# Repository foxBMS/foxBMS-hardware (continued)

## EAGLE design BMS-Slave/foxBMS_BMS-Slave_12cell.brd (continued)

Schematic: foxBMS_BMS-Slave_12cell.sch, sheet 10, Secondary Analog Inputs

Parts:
C1001: 100nF, 20%, 16V; C_SMD_0603_(1608)_R_KEMET_REV01
C1002, C1003, C1006, C1007, C1008: 1uF, 20%, 16V; C_SMD_0603_(1608)_R_KEMET_REV01
C1004, C1005: 10nF, 100V, 10%; C_SMD_0603_(1608)_R_KEMET_REV01
IC1001, IC1002, IC1005: ADG728BRUZ; SOP65P638X110-16N
IC1003, IC1004: LTC6255CS6; IC_SMD_TSOT-23-6_(S6)_R_LINEAR_REV01
R1001, R1002, R1003, R1004, R1005, R1006, R1007, R1008: 10,0K_0603_R_VISHAY_1%_TK100_REV_01; R_SMD_0603_R_VISHAY_REV01
R1009, R1010: 100R_0603_R_VISHAY_1%_TK100_REV_01; R_SMD_0603_R_VISHAY_REV01
SJ1001, SJ1002: OPT; CUSTOM_JUMPER_SJ

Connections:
+3.0V_VREF2_1: C1001.2, R1001.2, R1002.2, R1003.2, R1004.2, R1005.2, R1006.2, R1007.2, R1008.2; also elsewhere on the board
+5.0V_VREG_1: C1002.2, C1003.2, C1006.2, C1007.2, C1008.2, IC1001.2 (!RESET), IC1001.13 (VCC), IC1002.2 (!RESET), IC1002.13 (VCC), IC1002.15 (A1), IC1003.6 (V+), IC1004.6 (V+), IC1005.2 (!RESET), IC1005.13 (VCC), IC1005.16 (A0); also elsewhere on the board
FUSED_VBAT-: C1001.1, C1002.1, C1003.1, C1004.1, C1005.1, C1006.1, C1007.1, C1008.1, IC1001.14 (GND), IC1001.15 (A1), IC1001.16 (A0), IC1002.14 (GND), IC1002.16 (A0), IC1003.2 (V-), IC1004.2 (V-), IC1005.14 (GND), IC1005.15 (A1), SJ1001.2, SJ1002.2; also elsewhere on the board
unnamed: IC1003.1 (VOUT), IC1003.4 (-), R1009.1
unnamed: IC1003.5 (!SHDN), SJ1001.1
unnamed: IC1004.1 (VOUT), IC1004.4 (-), R1010.1
unnamed: IC1004.5 (!SHDN), SJ1002.1
SECONDARY-ANALOG-IN_0: IC1005.4 (S1); also elsewhere on the board
SECONDARY-ANALOG-IN_1: IC1005.5 (S2); also elsewhere on the board
SECONDARY-ANALOG-IN_2: IC1005.6 (S3); also elsewhere on the board
SECONDARY-ANALOG-IN_3: IC1005.7 (S4); also elsewhere on the board
SECONDARY-ANALOG-IN_4: IC1005.12 (S5); also elsewhere on the board
SECONDARY-ANALOG-IN_5: IC1005.11 (S6); also elsewhere on the board
SECONDARY-ANALOG-IN_6: IC1005.10 (S7); also elsewhere on the board
SECONDARY-ANALOG-IN_7: IC1005.9 (S8); also elsewhere on the board
SECONDARY-ANALOG-IN_8: IC1002.4 (S1); also elsewhere on the board
SECONDARY-ANALOG-IN_9: IC1002.5 (S2); also elsewhere on the board
SECONDARY-ANALOG-IN_10: IC1002.6 (S3); also elsewhere on the board
SECONDARY-ANALOG-IN_11: IC1002.7 (S4); also elsewhere on the board
SECONDARY-ANALOG-IN_12: IC1002.12 (S5); also elsewhere on the board
SECONDARY-ANALOG-IN_13: IC1002.11 (S6); also elsewhere on the board
SECONDARY-ANALOG-IN_14: IC1002.10 (S7); also elsewhere on the board
SECONDARY-ANALOG-IN_15: IC1002.9 (S8); also elsewhere on the board
SECONDARY-MUX-DATA_TEMP: C1004.2, R1009.2; also elsewhere on the board
SECONDARY-MUX-DATA_USER: C1005.2, R1010.2; also elsewhere on the board
SECONDARY-OPA_TEMP: IC1001.8 (D), IC1003.3 (+)
SECONDARY-OPA_USER: IC1002.8 (D), IC1004.3 (+), IC1005.8 (D)
SECONDARY-SCL_1: IC1001.1 (SCL), IC1002.1 (SCL), IC1005.1 (SCL); also elsewhere on the board
SECONDARY-SDA_1: IC1001.3 (SDA), IC1002.3 (SDA), IC1005.3 (SDA); also elsewhere on the board
SECONDARY-T-SENSOR_0: IC1001.4 (S1), R1008.1; also elsewhere on the board
SECONDARY-T-SENSOR_1: IC1001.5 (S2), R1007.1; also elsewhere on the board
SECONDARY-T-SENSOR_2: IC1001.6 (S3), R1006.1; also elsewhere on the board
SECONDARY-T-SENSOR_3: IC1001.7 (S4), R1005.1; also elsewhere on the board
SECONDARY-T-SENSOR_4: IC1001.12 (S5), R1004.1; also elsewhere on the board
SECONDARY-T-SENSOR_5: IC1001.11 (S6), R1003.1; also elsewhere on the board
SECONDARY-T-SENSOR_6: IC1001.10 (S7), R1002.1; also elsewhere on the board
SECONDARY-T-SENSOR_7: IC1001.9 (S8), R1001.1; also elsewhere on the board

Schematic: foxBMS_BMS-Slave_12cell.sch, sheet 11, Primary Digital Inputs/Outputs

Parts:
C1101: 100nF, 20%, 16V; C_SMD_0603_(1608)_R_KEMET_REV01
IC1101: PCA8574TS; SOP65P640X150-20N
R1101, R1102, R1103, R1104, R1105, R1106, R1107, R1108: 10,0K_0603_R_VISHAY_1%_TK100_REV_01; R_SMD_0603_R_VISHAY_REV01

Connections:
+5.0V_VREG_0: C1101.2, IC1101.5 (VDD), R1101.2, R1102.2, R1103.2, R1104.2, R1105.2, R1106.2, R1107.2, R1108.2; also elsewhere on the board
FUSED_VBAT-: C1101.1, IC1101.6 (A0), IC1101.7 (A1), IC1101.9 (A2), IC1101.15 (VSS); also elsewhere on the board
PRIMARY-DIGITAL-IO_0: IC1101.10 (P0), R1101.1; also elsewhere on the board
PRIMARY-DIGITAL-IO_1: IC1101.11 (P1), R1102.1; also elsewhere on the board
PRIMARY-DIGITAL-IO_2: IC1101.12 (P2), R1103.1; also elsewhere on the board
PRIMARY-DIGITAL-IO_3: IC1101.14 (P3), R1104.1; also elsewhere on the board
PRIMARY-DIGITAL-IO_4: IC1101.16 (P4), R1105.1; also elsewhere on the board
PRIMARY-DIGITAL-IO_5: IC1101.17 (P5), R1106.1; also elsewhere on the board
PRIMARY-DIGITAL-IO_6: IC1101.19 (P6), R1107.1; also elsewhere on the board
PRIMARY-DIGITAL-IO_7: IC1101.20 (P7), R1108.1; also elsewhere on the board
PRIMARY-SCL_0: IC1101.2 (SCL); also elsewhere on the board
PRIMARY-SDA_0: IC1101.4 (SDA); also elsewhere on the board

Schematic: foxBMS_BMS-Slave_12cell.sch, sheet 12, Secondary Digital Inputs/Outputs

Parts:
C1201: 100nF, 20%, 16V; C_SMD_0603_(1608)_R_KEMET_REV01
IC1201: PCA8574TS; SOP65P640X150-20N
R1201, R1202, R1203, R1204, R1205, R1206, R1207, R1208: 10,0K_0603_R_VISHAY_1%_TK100_REV_01; R_SMD_0603_R_VISHAY_REV01

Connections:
+5.0V_VREG_1: C1201.2, IC1201.5 (VDD), R1201.2, R1202.2, R1203.2, R1204.2, R1205.2, R1206.2, R1207.2, R1208.2; also elsewhere on the board
FUSED_VBAT-: C1201.1, IC1201.6 (A0), IC1201.7 (A1), IC1201.9 (A2), IC1201.15 (VSS); also elsewhere on the board
SECONDARY-DIGITAL-IO_0: IC1201.10 (P0), R1201.1; also elsewhere on the board
SECONDARY-DIGITAL-IO_1: IC1201.11 (P1), R1202.1; also elsewhere on the board
SECONDARY-DIGITAL-IO_2: IC1201.12 (P2), R1203.1; also elsewhere on the board
SECONDARY-DIGITAL-IO_3: IC1201.14 (P3), R1204.1; also elsewhere on the board
SECONDARY-DIGITAL-IO_4: IC1201.16 (P4), R1205.1; also elsewhere on the board
SECONDARY-DIGITAL-IO_5: IC1201.17 (P5), R1206.1; also elsewhere on the board
SECONDARY-DIGITAL-IO_6: IC1201.19 (P6), R1207.1; also elsewhere on the board
SECONDARY-DIGITAL-IO_7: IC1201.20 (P7), R1208.1; also elsewhere on the board
SECONDARY-SCL_1: IC1201.2 (SCL); also elsewhere on the board
SECONDARY-SDA_1: IC1201.4 (SDA); also elsewhere on the board

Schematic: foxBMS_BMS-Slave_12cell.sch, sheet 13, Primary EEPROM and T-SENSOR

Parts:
C1301, C1302: 100nF, 20%, 16V; C_SMD_0603_(1608)_R_KEMET_REV01
IC1301: M24M02-DR; SOIC127P600X175-8N
IC1302: MCP9800A0T-M/OT; SOT95P280X145-5N
R1301, R1302: 10,0K_0603_R_VISHAY_1%_TK100_REV_01; R_SMD_0603_R_VISHAY_REV01

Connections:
+5.0V_VREG_0: C1301.2, C1302.2, IC1301.8 (VCC), IC1302.1 (VDD), R1301.2, R1302.2; also elsewhere on the board
FUSED_VBAT-: C1301.1, C1302.1, IC1301.3 (E2), IC1301.4 (VSS), IC1302.2 (GND); also elsewhere on the board
unnamed: IC1301.7 (!WC), R1302.1
PRIMARY-SCL_0: IC1301.6 (SCL), IC1302.4 (SCLK); also elsewhere on the board
PRIMARY-SDA_0: IC1301.5 (SDA), IC1302.5 (SDA); also elsewhere on the board
PRIMARY-TEMP-ALERT: IC1302.3 (ALERT), R1301.1; also elsewhere on the board

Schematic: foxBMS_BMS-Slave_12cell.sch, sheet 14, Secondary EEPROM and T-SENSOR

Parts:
C1401, C1402: 100nF, 20%, 16V; C_SMD_0603_(1608)_R_KEMET_REV01
IC1401: M24M02-DR; SOIC127P600X175-8N
IC1402: MCP9800A0T-M/OT; SOT95P280X145-5N
R1401, R1402: 10,0K_0603_R_VISHAY_1%_TK100_REV_01; R_SMD_0603_R_VISHAY_REV01

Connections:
+5.0V_VREG_1: C1401.2, C1402.2, IC1401.8 (VCC), IC1402.1 (VDD), R1401.2, R1402.2; also elsewhere on the board
FUSED_VBAT-: C1401.1, C1402.1, IC1401.3 (E2), IC1401.4 (VSS), IC1402.2 (GND); also elsewhere on the board
unnamed: IC1401.7 (!WC), R1402.1
SECONDARY-SCL_1: IC1401.6 (SCL), IC1402.4 (SCLK); also elsewhere on the board
SECONDARY-SDA_1: IC1401.5 (SDA), IC1402.5 (SDA); also elsewhere on the board
SECONDARY-TEMP-ALERT: IC1402.3 (ALERT), R1401.1; also elsewhere on the board

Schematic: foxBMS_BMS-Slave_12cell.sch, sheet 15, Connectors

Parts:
C1501, C1502, C1503, C1504, C1505, C1506, C1507, C1508: 100nF, 20%, 16V; C_SMD_0603_(1608)_R_KEMET_REV01
X1501, X1502: MA09-2
X1503: 43045-2400_MOLEX_24PIN; X_TH_MOLEX_43045-2400_R_REV01
X1504, X1505: MA05-2
X1506, X1507: 43045-1600_MOLEX_16PIN; X_TH_MOLEX_43045-1600_R_REV01
X1508: MA10-2
X1509, X1510, X1511, X1512, X1513, X1514: 43045-0200_MOLEX_2PIN; X_TH_MOLEX_43045-0200_R_REV01
X1515: MA02-2_TH; MA02-2

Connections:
+3.0V_VREF2_0: C1501.2, C1506.2, X1501.17, X1508.1; also elsewhere on the board
+3.0V_VREF2_1: C1502.2, C1507.2, X1502.17, X1508.2; also elsewhere on the board
+5.0V_VREG_0: C1503.2, C1505.2, X1504.9, X1508.3; also elsewhere on the board
+5.0V_VREG_1: C1504.2, C1508.2, X1505.9, X1508.4; also elsewhere on the board
CELL_0+: X1503.2; also elsewhere on the board
CELL_0-: X1503.13; also elsewhere on the board
CELL_1+: X1503.14; also elsewhere on the board
CELL_2+: X1503.3; also elsewhere on the board
CELL_3+: X1503.15; also elsewhere on the board
CELL_4+: X1503.4; also elsewhere on the board
CELL_5+: X1503.16; also elsewhere on the board
CELL_6+: X1503.5; also elsewhere on the board
CELL_7+: X1503.17; also elsewhere on the board
CELL_8+: X1503.6; also elsewhere on the board
CELL_9+: X1503.18; also elsewhere on the board
CELL_10+: X1503.7; also elsewhere on the board
CELL_11+: X1503.19; also elsewhere on the board
EXT_DC_IN+: X1513.1, X1514.1, X1515.1, X1515.3; also elsewhere on the board
EXT_DC_IN-: X1513.2, X1514.2, X1515.2, X1515.4; also elsewhere on the board
FUSED_VBAT-: C1501.1, C1502.1, C1503.1, C1504.1, C1505.1, C1506.1, C1507.1, C1508.1, X1501.18, X1502.18, X1504.10, X1505.10, X1506.9, X1506.10, X1506.11, X1506.12, X1506.13, X1506.14, X1506.15, X1506.16, X1507.9, X1507.10, X1507.11, X1507.12, X1507.13, X1507.14, X1507.15, X1507.16, X1508.19, X1508.20; also elsewhere on the board
PRIMARY-ANALOG-IN_0: X1501.1; also elsewhere on the board
PRIMARY-ANALOG-IN_1: X1501.2; also elsewhere on the board
PRIMARY-ANALOG-IN_2: X1501.3; also elsewhere on the board
PRIMARY-ANALOG-IN_3: X1501.4; also elsewhere on the board
PRIMARY-ANALOG-IN_4: X1501.5; also elsewhere on the board
PRIMARY-ANALOG-IN_5: X1501.6; also elsewhere on the board
PRIMARY-ANALOG-IN_6: X1501.7; also elsewhere on the board
PRIMARY-ANALOG-IN_7: X1501.8; also elsewhere on the board
PRIMARY-ANALOG-IN_8: X1501.9; also elsewhere on the board
PRIMARY-ANALOG-IN_9: X1501.10; also elsewhere on the board
PRIMARY-ANALOG-IN_10: X1501.11; also elsewhere on the board
PRIMARY-ANALOG-IN_11: X1501.12; also elsewhere on the board
PRIMARY-ANALOG-IN_12: X1501.13; also elsewhere on the board
PRIMARY-ANALOG-IN_13: X1501.14; also elsewhere on the board
PRIMARY-ANALOG-IN_14: X1501.15; also elsewhere on the board
PRIMARY-ANALOG-IN_15: X1501.16; also elsewhere on the board
PRIMARY-DIGITAL-IO_0: X1504.1; also elsewhere on the board
PRIMARY-DIGITAL-IO_1: X1504.2; also elsewhere on the board
PRIMARY-DIGITAL-IO_2: X1504.3; also elsewhere on the board
PRIMARY-DIGITAL-IO_3: X1504.4; also elsewhere on the board
PRIMARY-DIGITAL-IO_4: X1504.5; also elsewhere on the board
PRIMARY-DIGITAL-IO_5: X1504.6; also elsewhere on the board
PRIMARY-DIGITAL-IO_6: X1504.7; also elsewhere on the board
PRIMARY-DIGITAL-IO_7: X1504.8; also elsewhere on the board
PRIMARY-GPIO1-OPT: X1508.5; also elsewhere on the board
PRIMARY-GPIO2-OPT: X1508.7; also elsewhere on the board
PRIMARY-GPIO3-OPT: X1508.9; also elsewhere on the board
PRIMARY-GPIO4-OPT: X1508.11; also elsewhere on the board
PRIMARY-GPIO5-OPT: X1508.13; also elsewhere on the board
PRIMARY-IN+: X1509.1; also elsewhere on the board
PRIMARY-IN-: X1509.2; also elsewhere on the board
PRIMARY-OUT+: X1510.1; also elsewhere on the board
PRIMARY-OUT-: X1510.2; also elsewhere on the board
PRIMARY-T-SENSOR_0: X1506.1; also elsewhere on the board
PRIMARY-T-SENSOR_1: X1506.2; also elsewhere on the board
PRIMARY-T-SENSOR_2: X1506.3; also elsewhere on the board
PRIMARY-T-SENSOR_3: X1506.4; also elsewhere on the board
PRIMARY-T-SENSOR_4: X1506.5; also elsewhere on the board
PRIMARY-T-SENSOR_5: X1506.6; also elsewhere on the board
PRIMARY-T-SENSOR_6: X1506.7; also elsewhere on the board
PRIMARY-T-SENSOR_7: X1506.8; also elsewhere on the board
PRIMARY-TEMP-ALERT: X1508.17; also elsewhere on the board
PRIMARY-WDT: X1508.15; also elsewhere on the board
SECONDARY-ANALOG-IN_0: X1502.1; also elsewhere on the board
SECONDARY-ANALOG-IN_1: X1502.2; also elsewhere on the board
SECONDARY-ANALOG-IN_2: X1502.3; also elsewhere on the board
SECONDARY-ANALOG-IN_3: X1502.4; also elsewhere on the board
SECONDARY-ANALOG-IN_4: X1502.5; also elsewhere on the board
SECONDARY-ANALOG-IN_5: X1502.6; also elsewhere on the board
SECONDARY-ANALOG-IN_6: X1502.7; also elsewhere on the board
SECONDARY-ANALOG-IN_7: X1502.8; also elsewhere on the board
SECONDARY-ANALOG-IN_8: X1502.9; also elsewhere on the board
SECONDARY-ANALOG-IN_9: X1502.10; also elsewhere on the board
SECONDARY-ANALOG-IN_10: X1502.11; also elsewhere on the board
SECONDARY-ANALOG-IN_11: X1502.12; also elsewhere on the board
SECONDARY-ANALOG-IN_12: X1502.13; also elsewhere on the board
SECONDARY-ANALOG-IN_13: X1502.14; also elsewhere on the board
SECONDARY-ANALOG-IN_14: X1502.15; also elsewhere on the board
SECONDARY-ANALOG-IN_15: X1502.16; also elsewhere on the board
SECONDARY-DIGITAL-IO_0: X1505.1; also elsewhere on the board
SECONDARY-DIGITAL-IO_1: X1505.2; also elsewhere on the board
SECONDARY-DIGITAL-IO_2: X1505.3; also elsewhere on the board
SECONDARY-DIGITAL-IO_3: X1505.4; also elsewhere on the board
SECONDARY-DIGITAL-IO_4: X1505.5; also elsewhere on the board
SECONDARY-DIGITAL-IO_5: X1505.6; also elsewhere on the board
SECONDARY-DIGITAL-IO_6: X1505.7; also elsewhere on the board
SECONDARY-DIGITAL-IO_7: X1505.8; also elsewhere on the board
SECONDARY-GPIO1-OPT: X1508.6; also elsewhere on the board
SECONDARY-GPIO2-OPT: X1508.8; also elsewhere on the board
SECONDARY-GPIO3-OPT: X1508.10; also elsewhere on the board
SECONDARY-GPIO4-OPT: X1508.12; also elsewhere on the board
SECONDARY-GPIO5-OPT: X1508.14; also elsewhere on the board
SECONDARY-IN+: X1511.1; also elsewhere on the board
SECONDARY-IN-: X1511.2; also elsewhere on the board
SECONDARY-OUT+: X1512.1; also elsewhere on the board
SECONDARY-OUT-: X1512.2; also elsewhere on the board
SECONDARY-T-SENSOR_0: X1507.1; also elsewhere on the board
SECONDARY-T-SENSOR_1: X1507.2; also elsewhere on the board
SECONDARY-T-SENSOR_2: X1507.3; also elsewhere on the board
SECONDARY-T-SENSOR_3: X1507.4; also elsewhere on the board
SECONDARY-T-SENSOR_4: X1507.5; also elsewhere on the board
SECONDARY-T-SENSOR_5: X1507.6; also elsewhere on the board
SECONDARY-T-SENSOR_6: X1507.7; also elsewhere on the board
SECONDARY-T-SENSOR_7: X1507.8; also elsewhere on the board
SECONDARY-TEMP-ALERT: X1508.18; also elsewhere on the board
SECONDARY-WDT: X1508.16; also elsewhere on the board
VBAT+: X1503.8; also elsewhere on the board
VBAT-: X1503.1; also elsewhere on the board

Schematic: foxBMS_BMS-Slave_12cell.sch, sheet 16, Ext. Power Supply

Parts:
C1601: 1,00µF_0805_25V_X7R_KEMET; C_SMD_0805_(2012)_R_KEMET_REV01
C1602, C1603: 10µF_1210_25V_X7R; 1210
C1604: 100nF, 20%, 16V; C_SMD_0603_(1608)_R_KEMET_REV01
C1605: 1uF, 20%, 16V; C_SMD_0603_(1608)_R_KEMET_REV01
C1606: 470PF_0805_50V_X7R_KEMET; C_SMD_0805_(2012)_R_KEMET_REV01
C1607: 4,7NF_1812; 1812
C1608, C1609, C1610: 4,70µF_1206_25V_X7R_KEMET; C_SMD_1206_(3216)_R_KEMET_REV01
D1601, D1603: DI_DFLS1100; POWER_DI_123
D1602: DI_DFLZ36; POWER_DI_123
D1604: DI_PDS3200; POWER_DI_5
D1605: MMSZ5263B; SOD123
F1601: 1,250A_LITTELFUSE_466_1206; R_SMD_CHIP_1206_R_LITTLEFUSE_REV_01
IC1601: LT8302; S8E
L1601: WE-74404042100; WE-LQS
R1601: 390K_0603_R_VISHAY_1%_TK100_REV_01; R_SMD_0603_R_VISHAY_REV01
R1602: 86,6K_0603_R_VISHAY_1%_TK100_REV_01; R_SMD_0603_R_VISHAY_REV01
R1603: 39,0R_0805_R_VISHAY_1%_TK100_REV_01; R_SMD_0805_R_VISHAY_REV01
R1604: DUMMY_R_CHIP_0603_R_VISHAY; R_SMD_0603_R_VISHAY_REV01
R1605: 127K_0603_R_VISHAY_1%_TK100_REV_01; R_SMD_0603_R_VISHAY_REV01
R1606: 10,0K_0603_R_VISHAY_1%_TK100_REV_01; R_SMD_0603_R_VISHAY_REV01
TP1601, TP1602, TP1603: CUSTOM_PAD_PAD_2.0X1.5MM; CUSTOM_PAD_PAD2.0X1.5MM
TR1601: WE_750313457; WUERTH_CUSTOM
X1601: MA02-1_TH; MA02-1A

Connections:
EXT_DC_IN+: F1601.P$1; also elsewhere on the board
EXT_DC_IN-: C1601.P$1, C1602.P$1, C1603.P$1, C1604.1, C1605.1, C1607.P$1, IC1601.4 (GND), IC1601.P$1 (GND), R1602.1, R1606.1, TP1601.P$1; also elsewhere on the board
EXT_DC_ISO+: C1608.P$2, C1609.P$2, C1610.P$2, D1604.K (C), D1605.C (K), X1601.1; also elsewhere on the board
FUSED_VBAT-: C1607.P$2, C1608.P$1, C1609.P$1, C1610.P$1, D1605.A, TP1603.P$1, TR1601.8 (PIN8), X1601.2; also elsewhere on the board
unnamed: C1604.2, IC1601.1 (EN/UVLO), R1601.1, R1602.2
unnamed: C1605.2, IC1601.2 (INTVCC)
unnamed: TR1601.6 (PIN6), TR1601.7 (PIN7)
unnamed: IC1601.7 (R_REF), R1604.2, R1606.2
unnamed: IC1601.6 (R_FB), R1605.1
unnamed: D1603.A, IC1601.5 (SW), R1603.1, R1605.2, TR1601.1 (PIN2), TR1601.2 (PIN2)
unnamed: IC1601.8 (TC), R1604.1
unnamed: D1604.A1 (A), D1604.A2 (A), TR1601.5 (PIN5)
unnamed: C1606.P$1, R1603.2
unnamed: D1601.A, F1601.P$2
unnamed: C1601.P$2, D1601.K (C), L1601.1, TP1602.P$1
unnamed: D1602.K (C), D1603.K (C)
unnamed: C1602.P$2, C1603.P$2, C1606.P$2, D1602.A, IC1601.3 (V_IN), L1601.2, R1601.2, TR1601.3 (PIN4), TR1601.4 (PIN4)

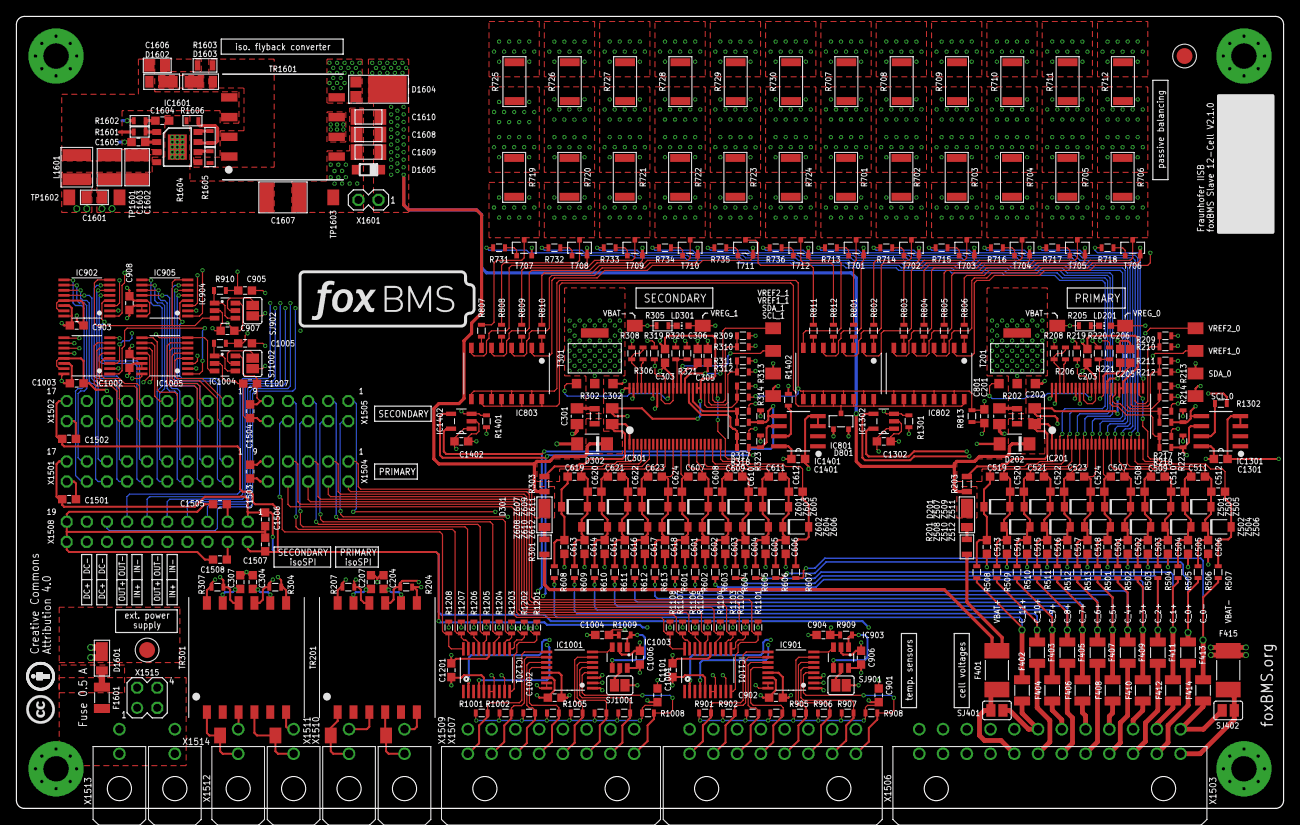
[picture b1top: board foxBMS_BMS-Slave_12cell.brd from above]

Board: 6 copper layers, 160.0 x 100.0 mm, 405 parts (0 on the bottom side), 274 nets.

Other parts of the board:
U$55, U$56: FIDUCIAL_1MM

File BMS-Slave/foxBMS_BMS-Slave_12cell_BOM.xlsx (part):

Pos. | Qty | Value | Device | Package | Parts | Description | Farnell | Digi-Key
 | Resistors
1 | 12 | 0R | 0,00R_0603_R_VISHAY_REV_01 | R_SMD_0603_R_VISHAY_REV01 | R210, R212, R214, R216, R218, R220, R310, R312, R314, R316, R318, R320 | 0,00R SMD - CHIP - Dickschichtwiderstand | 1469739
2 | 2 | 1.21k, 1%, 1/10W | 1,21K_0603_R_VISHAY_1%_TK100_REV_01 | R_SMD_0603_R_VISHAY_REV01 | R208, R308 | 1,21K SMD - CHIP - Dickschichtwiderstand | 1652852
3 | 36 | 10,0K_0603_R_VISHAY_1%_TK100_REV_01 | 10,0K_0603_R_VISHAY_1%_TK100_REV_01 | R_SMD_0603_R_VISHAY_REV01 | R813, R901, R902, R903, R904, R905, R906, R907, R908, R1001, R1002, R1003, R100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 | 10,0K SMD - CHIP - Dickschichtwiderstand | 1469748
4 | 4 | 100R, 1%, 1/10W | 100R_0805_R_VISHAY_1%_TK100_REV_01 | R_SMD_0805_R_VISHAY_REV01 | R202, R203, R302, R303 | 100R SMD - CHIP - Dickschichtwiderstand | 1469862
5 | 30 | 100R_0603_R_VISHAY_1%_TK100_REV_01 | 100R_0603_R_VISHAY_1%_TK100_REV_01 | R_SMD_0603_R_VISHAY_REV01 | R501, R502, R503, R504, R505, R506, R507, R508, R509, R510, R511, R512, R513, R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 | 100R SMD - CHIP - Dickschichtwiderstand | 1469752
6 | 4 | 120R, 1%, 1/10W | 120R_0603_R_VISHAY_1%_TK100_REV_01 | R_SMD_0603_R_VISHAY_REV01 | R204, R207, R304, R307 | 120R SMD - CHIP - Dickschichtwiderstand | 1652832
7 | 12 | 150R_0603_R_VISHAY_1%_TK100_REV_01 | 150R_0603_R_VISHAY_1%_TK100_REV_01 | R_SMD_0603_R_VISHAY_REV01 | R801, R802, R803, R804, R805, R806, R807, R808, R809, R810, R811, R812 | 150R SMD - CHIP - Dickschichtwiderstand | 1469760
8 | 2 | 1M, 10%, 1/10W | 1,00M_0603_R_VISHAY_1%_TK100_REV_01 | R_SMD_0603_R_VISHAY_REV01 | R219, R319 | 1,00M SMD - CHIP - Dickschichtwiderstand | 1469746
9 | 2 | 1M, 10%, 1/10W | 330R_0603_R_VISHAY_1%_TK100_REV_01 | R_SMD_0603_R_VISHAY_REV01 | R205, R305 | 330R SMD - CHIP - Dickschichtwiderstand | 2141320
10 | 12 | 3.3k, 10%, 1/10W | 3,30K_0603_R_VISHAY_1%_TK100_REV_01 | R_SMD_0603_R_VISHAY_REV01 | R713, R714, R715, R716, R717, R718, R731, R732, R733, R734, R735, R736 | 3,30K SMD - CHIP - Dickschichtwiderstand | 1469793
11 | 4 | 4.7k, 10%, 1/10W | 1,20K_0603_R_VISHAY_1%_TK100_REV_01 | R_SMD_0603_R_VISHAY_REV01 | R222, R223, R322, R323 | 1,20K SMD - CHIP - Dickschichtwiderstand | 1469741
12 | 24 | 75R, 10%, 0.4W | 68,0R_2010_R_YAGEO_5%_TK100_REV_01 | R_SMD_2010_R_YAGEO_REV01 | R701, R702, R703, R704, R705, R706, R707, R708, R709, R710, R711, R712, R719, R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 | 68,0R SMD - CHIP - Dickschichtwiderstand | 2323988
13 | 2 | 806, 1%, 1/10W | 820R_0603_R_VISHAY_1%_TK100_REV_01 | R_SMD_0603_R_VISHAY_REV01 | R206, R306 | 820R SMD - CHIP - Dickschichtwiderstand | 1469841
14 | 1 | 402K_0603_R_VISHAY_1%_TK100_REV_01 | 390K_0603_R_VISHAY_1%_TK100_REV_01 | R_SMD_0603_R_VISHAY_REV01 | R1601 | 390K SMD - CHIP - Dickschichtwiderstand | 2303278
15 | 1 | 86,6K_0603_R_VISHAY_1%_TK100_REV_01 | 86,6K_0603_R_VISHAY_1%_TK100_REV_01 | R_SMD_0603_R_VISHAY_REV01 | R1602 | 86,6K SMD - CHIP - Dickschichtwiderstand | 2059490
16 | 1 | 39,0R_0805_R_VISHAY_1%_TK100_REV_01 | 39,0R_0805_R_VISHAY_1%_TK100_REV_01 | R_SMD_0805_R_VISHAY_REV01 | R1603 | 39,0R SMD - CHIP - Dickschichtwiderstand | 1750736
17 | 1 | 127K_0603_R_VISHAY_1%_TK100_REV_01 | 127K_0603_R_VISHAY_1%_TK100_REV_01 | R_SMD_0603_R_VISHAY_REV01 | R1605 | 127K SMD - CHIP - Dickschichtwiderstand | 2059500
18 | 2 | 0,00R_0805_R_VISHAY_REV_01 | 0,00R_0805_R_VISHAY_REV_01 | R_SMD_0805_R_VISHAY_REV01 | R201, R301 | 0,00R SMD - CHIP - Dickschichtwiderstand | 2057661
 | Capacitors
19 | 4 | 100nF, 10%, 100V | 100NF_0805_100V_X7R_MULTICOMP | C_SMD_0805_(2012)_R_MULTICOMP_REV01 | C201 C202 C301 C302 | 100nF Keramik-Kondensator | 2320821
20 | 18 | 100nF, 20%, 16V | 100NF_0603_16V_X7R_KEMET | C_SMD_0603_(1608)_R_KEMET_REV01 | C801, C901, C1001, C1101, C1201, C1301, C1302, C1401, C1402, C1501, C1502, C150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 | 100nF Keramik-Kondensator | 2581045
21 | 4 | 100pF, 15%, 25V | 100PF_0603_50V_C0G_KEMET | C_SMD_0603_(1608)_R_KEMET_REV01 | C204, C207, C304, C307 | 100pF Keramik-Kondensator | 1414603
22 | 28 | 10nF, 100V, 10% | 10,0NF_0603__100V_X7R_KEMET | C_SMD_0603_(1608)_R_KEMET_REV01 | C501, C502, C503, C504, C505, C506, C513, C514, C515, C516, C517, C518, C601, C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 | 10,0nF Keramik-Kondensator | 1865545
23 | 17 | 1uF, 20%, 16V | 1,00µF_0603_16V_X7R_KEMET | C_SMD_0603_(1608)_R_KEMET_REV01 | C203, C205, C206, C303, C305, C306, C902, C903, C906, C907, C908, C1002, C1003,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 | 1,00µF Keramik-Kondensator | 1650837
24 | 1 |  | 1,00µF_0805_50V_X7R_KEMET | C_SMD_0805_(2012)_R_KEMET_REV01 | C1601 | 1,00µF Keramik-Kondensator | 2118131
25 | 2 |  | 10µF_1210_50V_X7R | 1210 | C1602, C1603 | 10µF Keramik-Kondensator | 2449143
26 | 1 |  | 470PF_0805_50V_X7R_KEMET | C_SMD_0805_(2012)_R_KEMET_REV01 | C1606 | 470pF Keramik-Kondensator | 1759283
27 | 1 |  | 4,7NF_1812_1kV | 1812 | C1607 | 4,7nF Keramik-Kondensator | 1702159
28 | 3 |  | 4,70µF_1206_100V_X7R_KEMET | C_SMD_1206_(3216)_R_KEMET_REV01 | C1608, C1609, C1610 | 4,70µF Keramik-Kondensator |  | 478-8719-1-ND
 | ICs
29 | 2 | 24AA02UID | M24M02-DR | SOIC127P600X175-8N | IC1301, IC1401 | EEPROM |  | 497-16238-1-ND
30 | 3 | ACPL-247-500E | ACPL-247-500E | OC_SMD_SOIC-16_R_AVAGO_REV01 | IC801, IC802, IC803 | ACPL-247 - AVAGO | 1634758
31 | 2 | PCF8574TS/3 | PCA8574TS/3 | SOP65P640X150-20N | IC1101, IC1201 | IC, I/O EXPANDER, 8BIT, I2C, 20SSOP | 1506642
32 | 6 | LTC1380CGN | ADG728BRUZ | IC_SMD_TSSOP-16 | IC901, IC902, IC905, IC1001, IC1002, IC1005 | ADG728BRUZ | 9604383
33 | 4 | LTC6255CS6 | LTC6255CS6 | IC_SMD_TSOT-23-6_(S6)_R_LINEAR_REV01 | IC903, IC904, IC1003, IC1004 | LTC6255 Serie - Linear |  | LTC6255CS6#TRMPBFCT-ND
34 | 2 | MCP9800A5T-M/OT | MCP9800A0T-M/OT | SOT95P280X145-5N | IC1302 IC1402 | Temperature Sensor | 1439485
35 | 2 | 0_LES_BATTERIE-MANAGEMENT.SMD_LTC6804HG-1 | 0_LES_BATTERIE-MANAGEMENT.SMD_LTC6811HG-1 | 0_LES_BATTERIE-MANAGEMENT.SMD_IC_SMD_SSOP-48_(G48)_R_LINEAR_REV01 | IC201 IC301 | LTC6811-1 - Linear Technology |  | LTC6811HG-1#PBF-ND
36 | 1 |  | LT8302 | S8E | IC1601 | LT8302 | 2366012
 | Diodes
37 | 24 | 6.8V, 500mW | MMSZ4692_T1G | D_SMD_SOD-123_R_ON_REV01 | Z501, Z502, Z503, Z504, Z505, Z506, Z507, Z508, Z509, Z510, Z511, Z512, Z601, Z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 | MMSZ4xxxT1G Serie - ON Semiconductor | 2463562
38 | 1 | BAT54C | BAT54C | D_SMD_SOT23_(TO-236AB)_R_NXP_REV01 | D801 |  | 1081192
39 | 2 | Green | LEDCHIP-LED0603 | CHIP-LED0603 | LD201 LD301 | LED | 2099223
40 | 2 | SMAJ60CA_VISHAY | SMAJ60CA_VISHAY | D_SMD_SMA_(DO-214AC)_(BIDIR)_R_VISHAY_REV01 | D202, D302 | SMAJ bi-directional Transient Voltage Suppressors | 1837055
41 | 1 |  | DI_PDS3200 | POWER_DI_5 | D1604 | Schottky Diode | 1713904
42 | 1 |  | MMSZ5263B | SOD123 | D1605 | Zener Diode |  | MMSZ5263BT1GOSCT-ND
43 | 3 |  | DI_DFLS1100 | POWER_DI_123 | D201, D301, D1601 | Schottky Diode | 1713889
 | Transistors
44 | 12 | NX2301P | NX2301P,215 | D_SMD_SOT23_(TO-236AB)_R_NXP_REV01 | T701, T702, T703, T704, T705, T706, T707, T708, T709, T710, T711, T712 | NX2301P - NXP | 1894738
45 | 2 | PBHV8115Z | PBHV8115Z | D_SMD_SOT223_(SC-73)_R_NXP_REV01 | T201 T301 | PBHV8115Z - NXP | 1829309
 | Misc
46 | 2 | HX1188NL | Pulse HM2102NL | HM2102NL | TR201, TR301 | HM2102NL
47 | 1 |  | WE_750313457 | WUERTH_CUSTOM | TR1601 | WE_750313457 Flyback Transformer |  | 1297-1136-1-ND
48 | 6 | CUSTOM_PAD_PAD_2.0X1.5MM | CUSTOM_PAD_PAD_2.0X1.5MM | CUSTOM_PAD_PAD2.0X1.5MM | TP206, TP209, TP210, TP306, TP309, TP310 | Harwin SMD Test Points |  | 952-2664-1-ND
49 | 13 | FUSE: 0.250A, 32V, 0.57R | 0,250A_LITTELFUSE_466_1206 | R_SMD_CHIP_1206_R_LITTLEFUSE_REV_01 | F402, F403, F404, F405, F406, F407, F408, F409, F410, F411, F412, F413, F414 | LITTELFUSE 0466.250NR SICHERUNG, 0.25A | 9921826
50 | 2 | 0.5A, 63V, 0.25R | 0,500A_LITTELFUSE_448 | 448_SERIES_LITTELFUSE | F401 F415 | LITTELFUSE 0448.500MR SICHERUNG, 500MA | 1596919
51 | 1 |  | 1,25A_LITTELFUSE_466_1206 | 1,25A_LITTELFUSE_466_1206 | R_SMD_CHIP_1206_R_LITTLEFUSE_REV_01 | F1601 | 1596526
52 | 1 |  | WE-74404042100 | WE-LQS | L1601 | Inductor | 2431496
 | Connectors
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
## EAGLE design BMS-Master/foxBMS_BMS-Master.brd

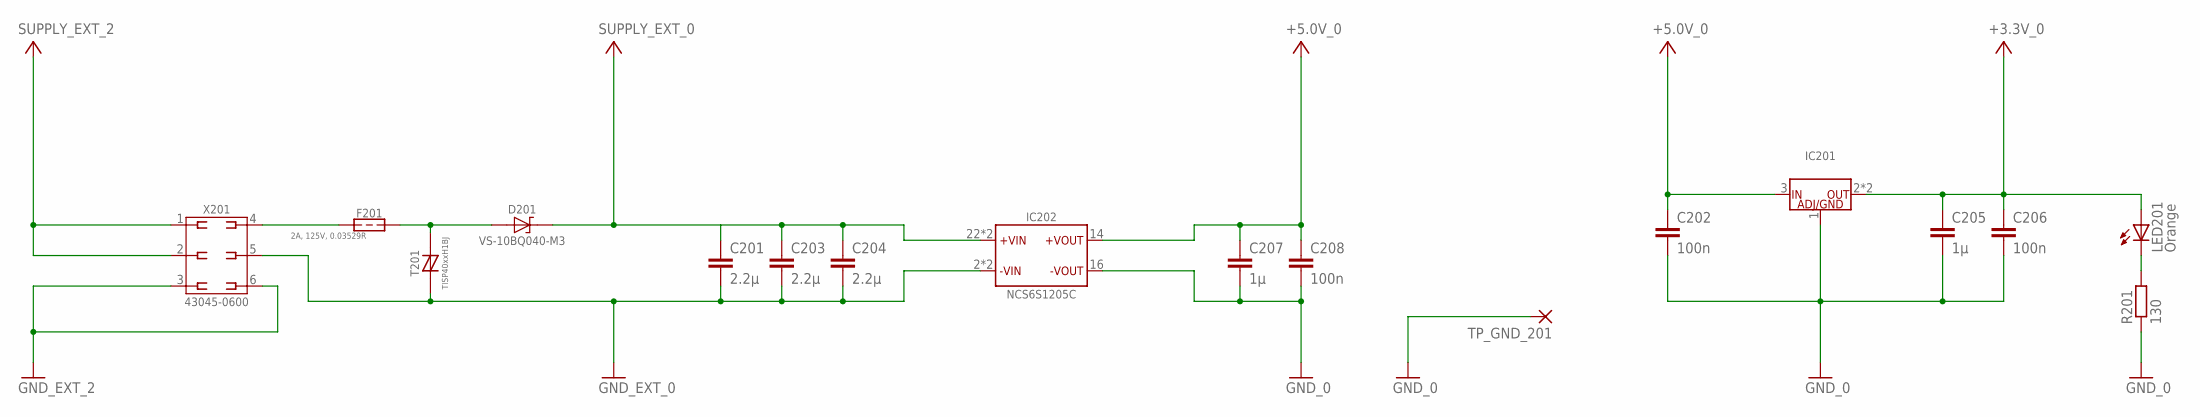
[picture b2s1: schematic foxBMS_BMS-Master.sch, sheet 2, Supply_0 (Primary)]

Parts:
C201, C203, C204: 2.2µ; C0805
C202, C206, C208: 100n; C0603
C205, C207: 1µ; C0603
D201: VS-10BQ040-M3; D_SMD_SMB_(DO-214AA)_R_VISHAY_REV01
F201: 0,500A_LITTELFUSE_4482A; 448_SERIES_LITTELFUSE
IC201: LM1085IS-5.0/NOPB; IC_SMD_TO-263-3_(KTT0003B)_R_TI_REV01
IC202: MURATA_NCS6S1205C; IC_TH_32,00MMX20,00MMX10,00MM_(7-PIN)_R_MURATA_REV01
LED201: Orange; CHIP-LED0603
R201: 130; R0603
T201: TISP40XXH1BJ; TVS_THYRISTOR
TP_GND_201: 1,6/0,8
X201: 43045-0600_MOLEX_6PIN; X_TH_MOLEX_43045-0600_R_REV01

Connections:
+3.3V_0: C205.1, C206.1, IC201.2 (OUT), IC201.4 (OUT), LED201.A; also elsewhere on the board
+5.0V_0: C202.1, C207.1, C208.1, IC201.3 (IN), IC202.14 (+VOUT); also elsewhere on the board
GND_0: C202.2, C205.2, C206.2, C207.2, C208.2, IC201.1 (ADJ/GND), IC202.16 (-VOUT), R201.1, TP_GND_201.1; also elsewhere on the board
GND_EXT_0: C201.2, C203.2, C204.2, IC202.2 (-VIN), IC202.3 (-VIN), T201.C (T), X201.5; also elsewhere on the board
GND_EXT_2: X201.3, X201.6; also elsewhere on the board
unnamed: LED201.C, R201.2
unnamed: D201.A, F201.P$2, T201.A (R)
unnamed: F201.P$1, X201.4
SUPPLY_EXT_0: C201.1, C203.1, C204.1, D201.C, IC202.22 (+VIN), IC202.23 (+VIN); also elsewhere on the board
SUPPLY_EXT_2: X201.1, X201.2; also elsewhere on the board

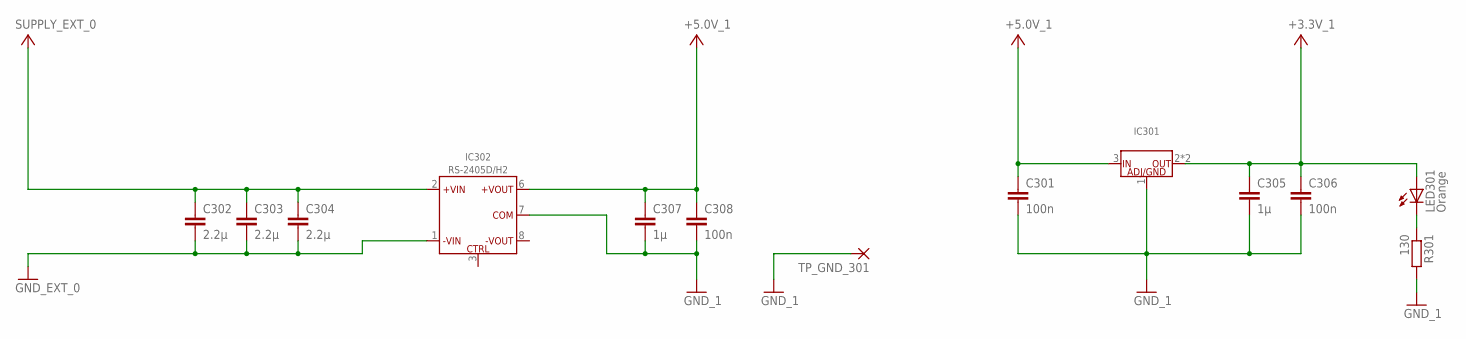
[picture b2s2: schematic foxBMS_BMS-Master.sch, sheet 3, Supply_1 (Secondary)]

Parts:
C301, C306, C308: 100n; C0603
C302, C303, C304: 2.2µ; C0805
C305, C307: 1µ; C0603
IC301: LM1085IS-5.0/NOPB; IC_SMD_TO-263-3_(KTT0003B)_R_TI_REV01
IC302: RS-2405D/H2; IC_TH_SIP8_R_RECOM_REV01
LED301: Orange; CHIP-LED0603
R301: 130; R0603
TP_GND_301: 1,6/0,8

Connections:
+3.3V_1: C305.1, C306.1, IC301.2 (OUT), IC301.4 (OUT), LED301.A; also elsewhere on the board
+5.0V_1: C301.1, C307.1, C308.1, IC301.3 (IN), IC302.6 (+VOUT); also elsewhere on the board
GND_1: C301.2, C305.2, C306.2, C307.2, C308.2, IC301.1 (ADJ/GND), IC302.7 (COM), R301.2, TP_GND_301.1; also elsewhere on the board
GND_EXT_0: C302.2, C303.2, C304.2, IC302.1 (-VIN); also elsewhere on the board
unnamed: LED301.C, R301.1
SUPPLY_EXT_0: C302.1, C303.1, C304.1, IC302.2 (+VIN); also elsewhere on the board
